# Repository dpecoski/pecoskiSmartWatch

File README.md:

# pecoskiSmartWatch
Dimitri Pecoski's Smart Watch Project

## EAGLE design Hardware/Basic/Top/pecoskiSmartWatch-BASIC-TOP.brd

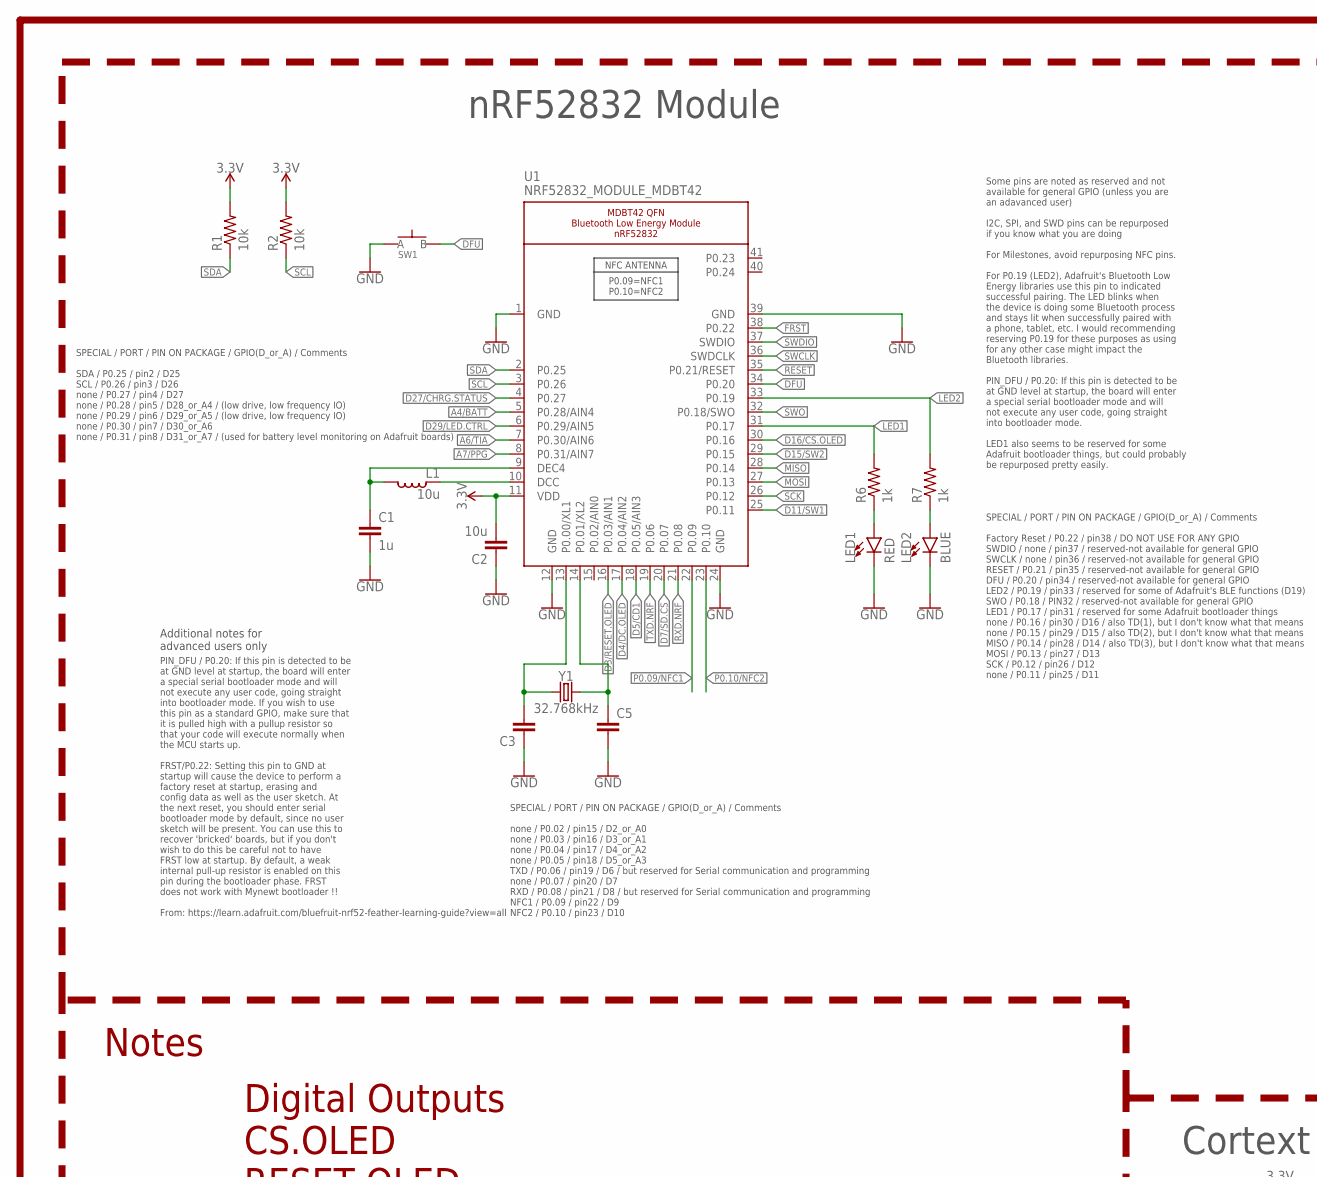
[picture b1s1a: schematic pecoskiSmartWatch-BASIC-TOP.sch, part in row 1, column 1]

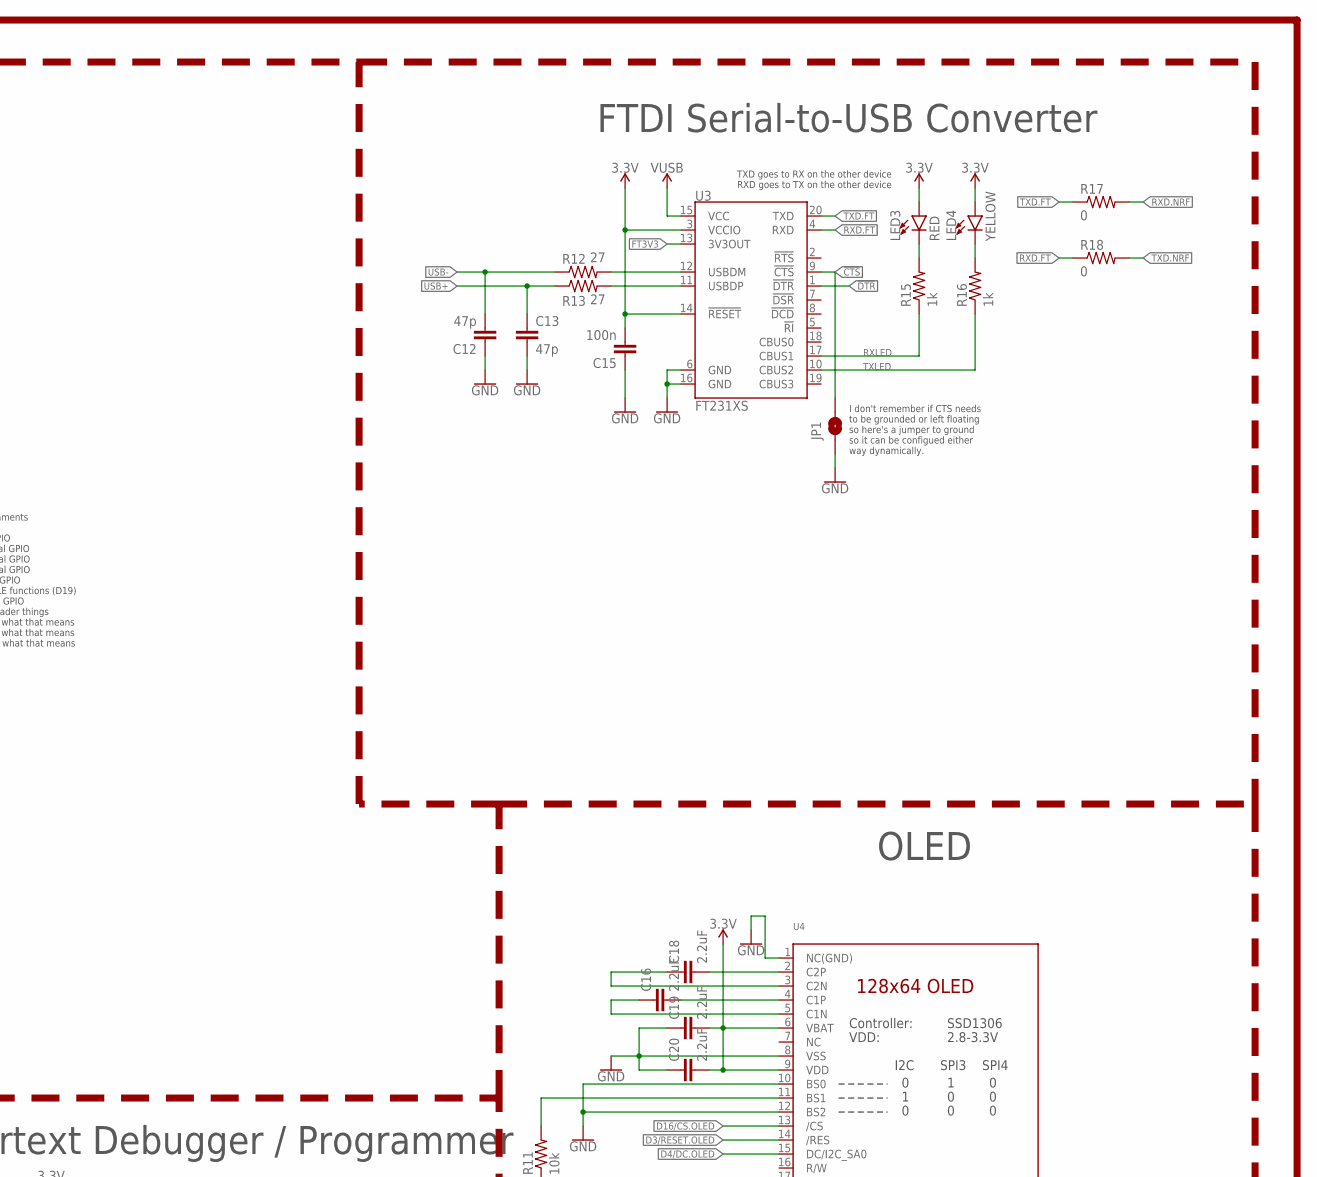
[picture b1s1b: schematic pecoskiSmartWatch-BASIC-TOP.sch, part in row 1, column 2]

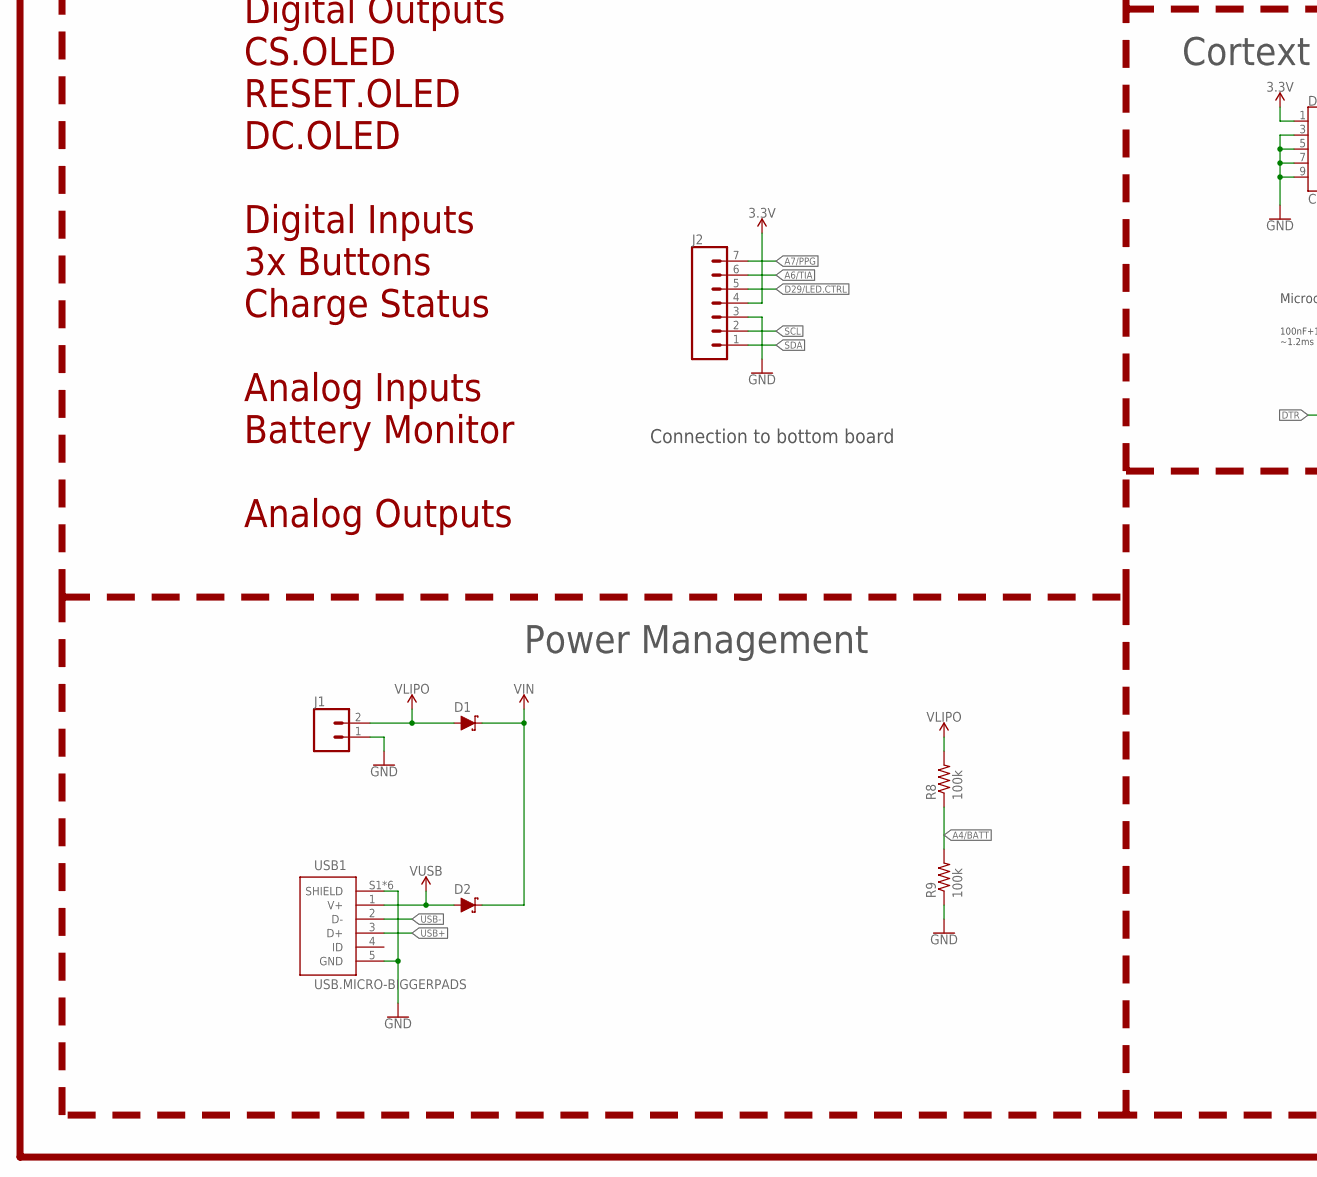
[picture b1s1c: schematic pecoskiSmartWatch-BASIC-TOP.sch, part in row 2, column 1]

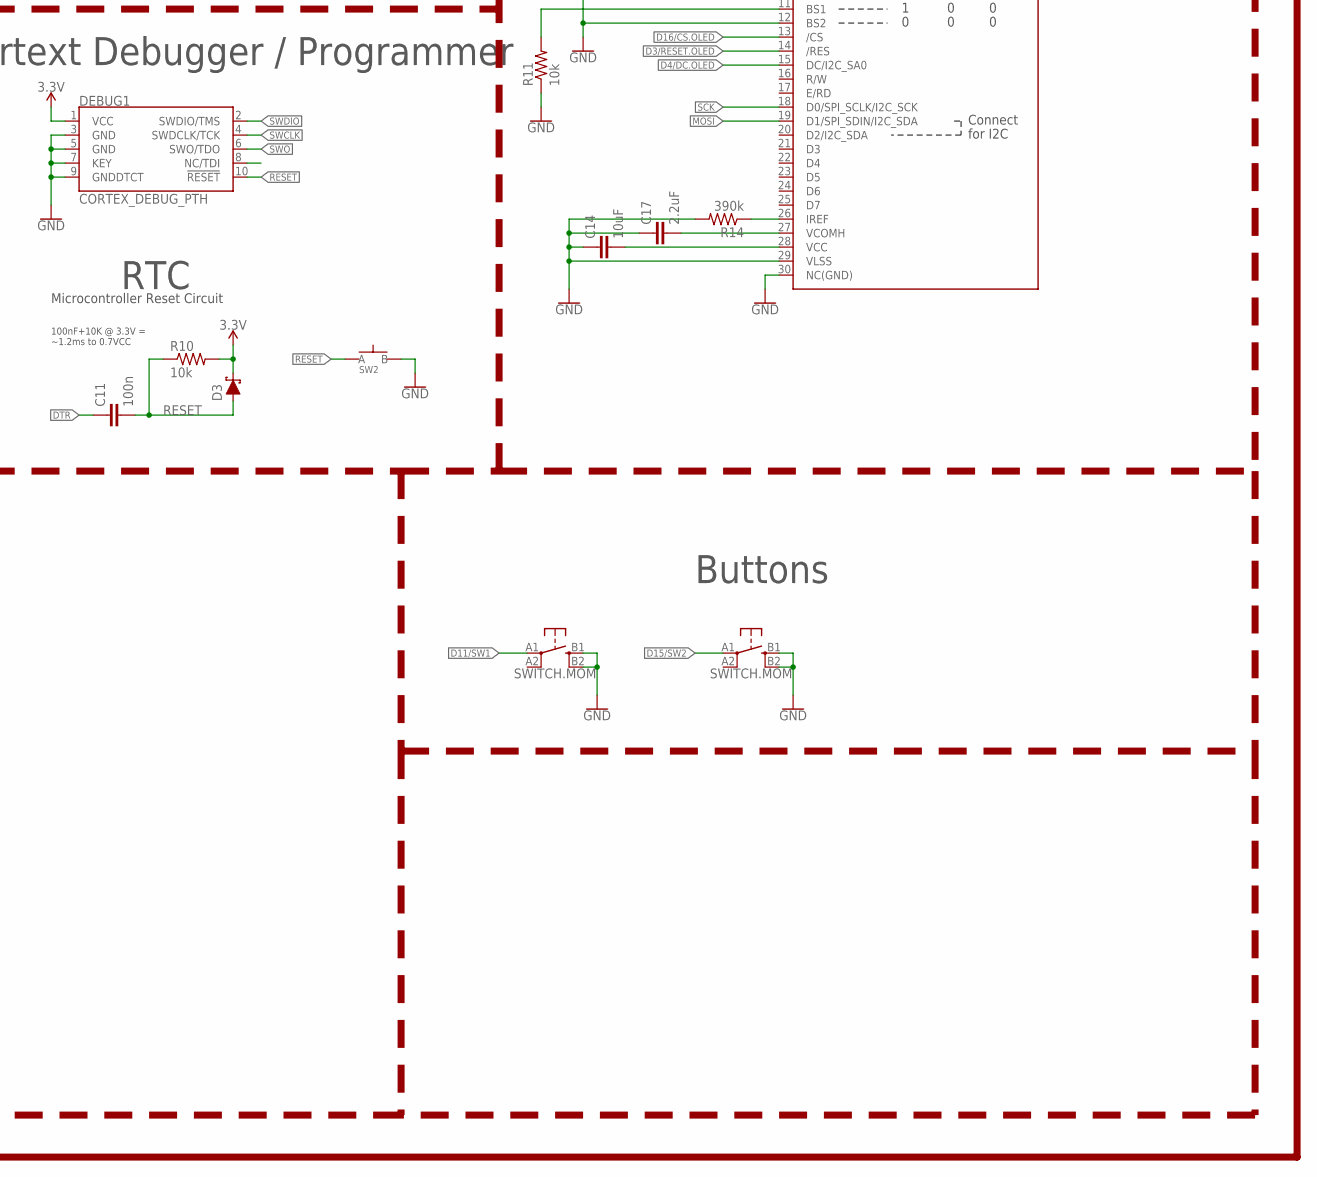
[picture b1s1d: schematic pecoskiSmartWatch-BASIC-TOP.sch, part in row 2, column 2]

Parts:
C1: 1u; C0603
C2: 10u; C0805
C3, C5: CAPACITOR0603; C0603
C11, C15: 100n; C0603
C12, C13: 47p; C0603
C14: 10uF; C0603
C16, C17, C18, C19, C20: 2.2uF; C0402
D1, D2, D3: SCHOTTKY-USC; USC
DEBUG1: CORTEX_DEBUG_PTH; 2X5-PTH-1.27MM
J1: CONN_02; 1X02
J2: CONN_07-1.27MM; 1X07_1.27MM
JP1: JUMPER-SMT_2_NO_SILK; SMT-JUMPER_2_NO_SILK
L1: 10u; L0603
LED1, LED3: RED; LED-0603
LED2: BLUE; LED-0603
LED4: YELLOW; LED-0603
R1, R2, R10, R11: 10k; R0603
R6, R7, R15, R16: 1k; R0603
R8, R9: 100k; R0603
R12, R13: 27; R0603
R14: 390k; R0603
R17, R18: 0; R0603
SW1, SW2: SPST-PTS830GG140-COPY.1-3; BUTTON-GULLWING
SW3, SW4: SWITCH.MOM; TACTILE_SWITCH_SMD_6.2MM_TALL
U1: NRF52832_MODULE_MDBT42; BLE_MODULE_RAYTAC_MDBT42
U3: FT231XS; SSOP20_L
U4: DISP_OLED_UG-2864HSWEG01-NO-WRAPAROUND; UG-2864HSWEG01_0.96IN_NO-WRAPAROUND
USB1: USB.MICRO-BIGGERPADS; USB-MICRO-01.BIGGERPADS
Y1: 32.768kHz; 2-SMD.NOLEAD.2.0MMTO1.2MM

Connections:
3.3V: C2.2, C15.2, C19.2, C20.2, D3.- (C), DEBUG1.1 (VCC), J2.4, LED3.A, LED4.A, R1.2, R2.2, R10.2, U1.11 (VDD), U3.3 (VCCIO), U3.14 (!RESET), U4.6 (VBAT), U4.9 (VDD)
!CTS: JP1.2, U3.9 (!CTS)
!DTR: U3.1 (!DTR)
A4/BATT: R8.1, R9.2, U1.5 (P0.28/AIN4)
A6/TIA: J2.6, U1.7 (P0.30/AIN6)
A7/PPG: J2.7, U1.8 (P0.31/AIN7)
D3/RESET.OLED: U1.16 (P0.03/AIN1), U4.14 (/RES)
D4/DC.OLED: U1.17 (P0.04/AIN2), U4.15 (DC/I2C_SA0)
D5/CD1: U1.18 (P0.05/AIN3)
D7/SD.CS: U1.20 (P0.07)
D11/SW1: SW3.A1 (1), U1.25 (P0.11)
D15/SW2: SW4.A1 (1), U1.29 (P0.15)
D16/CS.OLED: U1.30 (P0.16), U4.13 (/CS)
D27/CHRG.STATUS: U1.4 (P0.27)
D29/LED.CTRL: J2.5, U1.6 (P0.29/AIN5)
DFU: SW1.3 (B), U1.34 (P0.20)
DTR: C11.1
FRST: U1.38 (P0.22)
FT3V3: U3.13 (3V3OUT)
GND: C1.2, C2.1, C3.1, C5.2, C12.1, C13.2, C14.1, C15.1, C17.1, C19.1, C20.1, DEBUG1.3 (GND), DEBUG1.5 (GND), DEBUG1.7 (KEY), DEBUG1.9 (GNDDTCT), J1.1, J2.3, JP1.1, LED1.C, LED2.C, R9.1, R11.1, R14.2, SW1.1 (A), SW2.3 (B), SW3.B1 (3), SW3.B2 (4), SW4.B1 (3), SW4.B2 (4), U1.1 (GND), U1.12 (GND), U1.24 (GND), U1.39 (GND), U3.6 (GND), U3.16 (GND), U4.1 (NC(GND)), U4.8 (VSS), U4.10 (BS0), U4.12 (BS2), U4.29 (VLSS), U4.30 (NC(GND)), USB1.5 (GND), USB1.S1 (SHIELD), USB1.S2 (SHIELD), USB1.S3 (SHIELD), USB1.S4 (SHIELD), USB1.S5 (SHIELD), USB1.S6 (SHIELD)
LED1: R6.2, U1.31 (P0.17)
LED2: R7.2, U1.33 (P0.19)
MISO: U1.28 (P0.14)
MOSI: U1.27 (P0.13), U4.19 (D1/SPI_SDIN/I2C_SDA)
unnamed: R11.2, U4.11 (BS1)
unnamed: R14.1, U4.26 (IREF)
unnamed: C18.2, U4.2 (C2P)
unnamed: C3.2, U1.13 (P0.00/XL1), Y1.P$1 (1)
unnamed: C18.1, U4.3 (C2N)
unnamed: C5.1, U1.14 (P0.01/XL2), Y1.P$2 (2)
unnamed: C16.2, U4.4 (C1P)
unnamed: C16.1, U4.5 (C1N)
unnamed: LED1.A, R6.1
unnamed: LED2.A, R7.1
unnamed: L1.1, U1.10 (DCC)
unnamed: C1.1, L1.2, U1.9 (DEC4)
unnamed: C14.2, U4.28 (VCC)
unnamed: C17.2, U4.27 (VCOMH)
unnamed: R12.2, U3.12 (USBDM)
unnamed: R13.2, U3.11 (USBDP)
unnamed: LED3.C, R15.2
unnamed: LED4.C, R16.2
P0.09/NFC1: U1.22 (P0.09)
P0.10/NFC2: U1.23 (P0.10)
RESET: C11.2, D3.+ (A), DEBUG1.10 (!RESET), R10.1, SW2.1 (A), U1.35 (P0.21/RESET)
RXD.FT: R18.1, U3.4 (RXD)
RXD.NRF: R17.2, U1.21 (P0.08)
RXLED: R15.1, U3.17 (CBUS1)
SCK: U1.26 (P0.12), U4.18 (D0/SPI_SCLK/I2C_SCK)
SCL: J2.2, R2.1, U1.3 (P0.26)
SDA: J2.1, R1.1, U1.2 (P0.25)
SWCLK: DEBUG1.4 (SWDCLK/TCK), U1.36 (SWDCLK)
SWDIO: DEBUG1.2 (SWDIO/TMS), U1.37 (SWDIO)
SWO: DEBUG1.6 (SWO/TDO), U1.32 (P0.18/SWO)
TXD.FT: R17.1, U3.20 (TXD)
TXD.NRF: R18.2, U1.19 (P0.06)
TXLED: R16.1, U3.10 (CBUS2)
USB+: C13.1, R13.1, USB1.3 (D+)
USB-: C12.2, R12.1, USB1.2 (D-)
VIN: D1.- (C), D2.- (C)
VLIPO: D1.+ (A), J1.2, R8.2
V_USB: D2.+ (A), U3.15 (VCC), USB1.1 (V+)

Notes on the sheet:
Microcontroller Reset Circuit
100nF+10K @ 3.3V = ~1.2ms to 0.7VCC
SPECIAL / PORT / PIN ON PACKAGE / GPIO(D_or_A) / Comments SDA / P0.25 / pin2 / D25 SCL / P0.26 / pin3 / D26 none / P0.27 / pin4 / D27 none / P0.28 / pin5 / D28_or_A4 / (low drive, low frequency IO) none / P0.29 / pin6 / D29_or_A5 / (low drive, low frequency IO) none / P0.30 / pin7 / D30_or_A6 none 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
SPECIAL / PORT / PIN ON PACKAGE / GPIO(D_or_A) / Comments none / P0.02 / pin15 / D2_or_A0 none / P0.03 / pin16 / D3_or_A1 none / P0.04 / pin17 / D4_or_A2 none / P0.05 / pin18 / D5_or_A3 TXD / P0.06 / pin19 / D6 / but reserved for Serial communication and programming none / P0.07 / pin20 / D7 RXD / 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
SPECIAL / PORT / PIN ON PACKAGE / GPIO(D_or_A) / Comments Factory Reset / P0.22 / pin38 / DO NOT USE FOR ANY GPIO SWDIO / none / pin37 / reserved-not available for general GPIO SWCLK / none / pin36 / reserved-not available for general GPIO RESET / P0.21 / pin35 / reserved-not available for general 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
Some pins are noted as reserved and not available for general GPIO (unless you are an adavanced user) I2C, SPI, and SWD pins can be repurposed if you know what you are doing For Milestones, avoid repurposing NFC pins. For P0.19 (LED2), Adafruit's Bluetooth Low Energy libraries use this pin to indic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
PIN_DFU / P0.20: If this pin is detected to be at GND level at startup, the board will enter a special serial bootloader mode and will not execute any user code, going straight into bootloader mode. If you wish to use this pin as a standard GPIO, make sure that it is pulled high with a pullup resis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
Additional notes for advanced users only
nRF52832 Module
OLED
Power Management
Buttons
Cortext Debugger / Programmer
RTC
Digital Outputs CS.OLED RESET.OLED DC.OLED Digital Inputs 3x Buttons Charge Status Analog Inputs Battery Monitor Analog Outputs
TXD goes to RX on the other device RXD goes to TX on the other device
I don't remember if CTS needs to be grounded or left floating so here's a jumper to ground so it can be configued either way dynamically.
FTDI Serial-to-USB Converter
Notes
Connection to bottom board

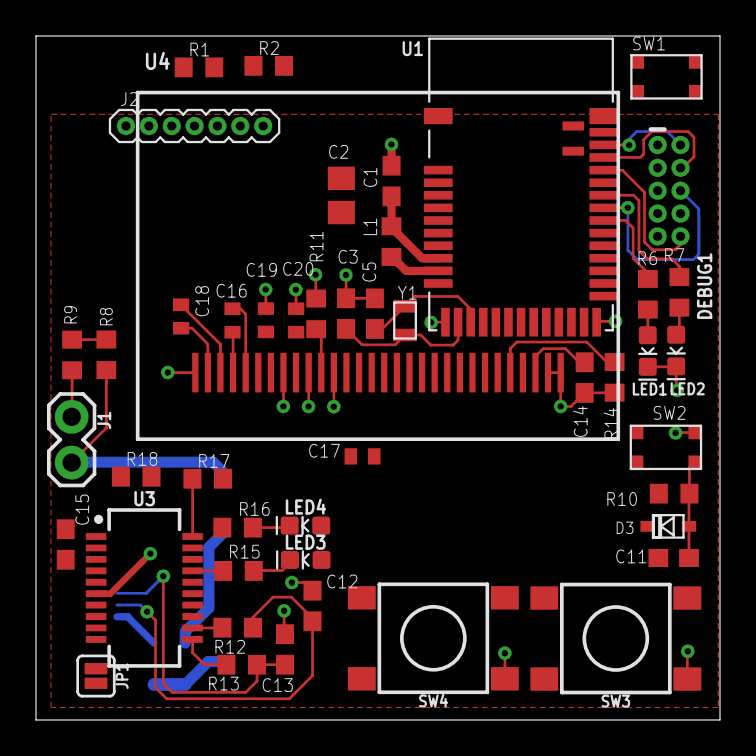
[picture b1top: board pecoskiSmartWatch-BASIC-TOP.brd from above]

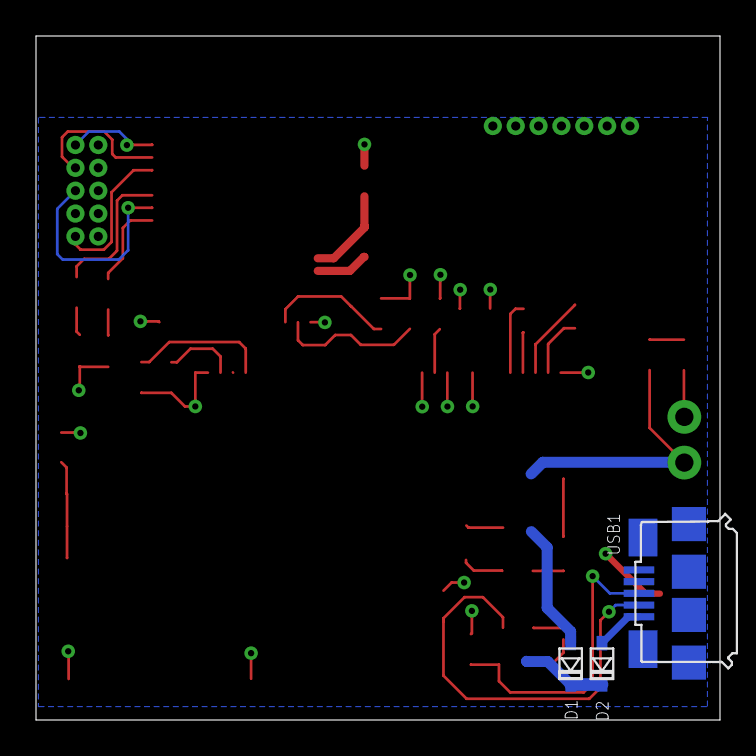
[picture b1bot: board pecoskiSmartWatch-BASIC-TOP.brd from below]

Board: 2 copper layers, 38.0 x 38.0 mm, 50 parts (3 on the bottom side), 52 nets.

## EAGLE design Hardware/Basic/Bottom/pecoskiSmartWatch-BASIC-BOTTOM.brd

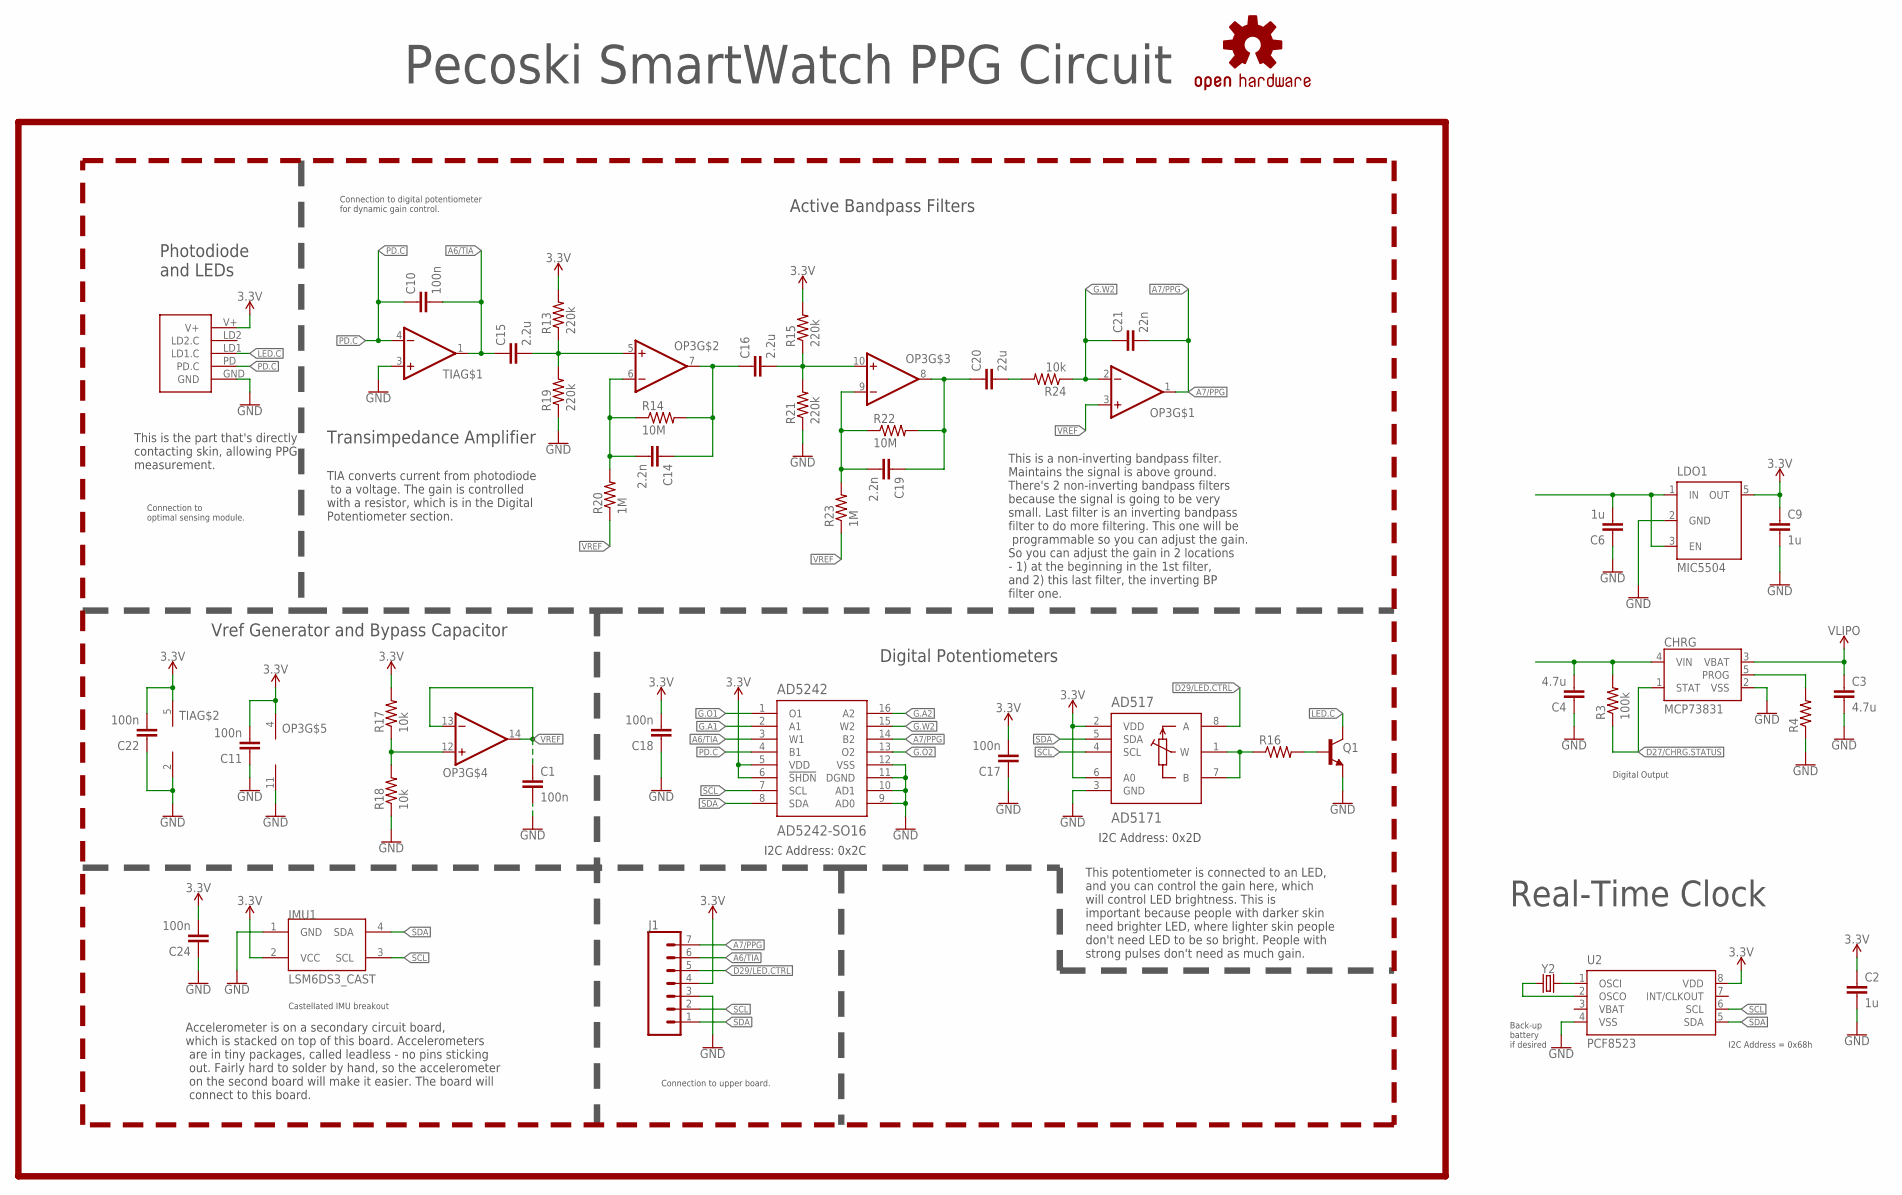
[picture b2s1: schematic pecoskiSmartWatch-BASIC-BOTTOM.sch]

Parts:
AD517: AD5171; SOT-23-8
AD5242: AD5242-SO16; SO16
C1, C10, C11, C17, C18, C22, C24: 100n; C0603
C2, C6, C9: 1u; C0603
C3, C4: 4.7u; C0603
C14, C19: 2.2n; C0603
C15, C16: 2.2u; C0603
C20: 22u; C0603
C21: 22n; C0603
CHRG: MCP73831; SOT23-5
IMU1: LSM6DS3_CAST
J1: CONN_07-1.27MM; 1X07_1.27MM
LDO1: MIC5504; SOT23-5
LOGO1: REVISION.A; REV.A
LOGO2: OSHW-LOGOS; OSHW-LOGO-S
OP3: OP-QUAD-SO14; SO14
Q1: NPN-GENERIC; SOT23-3
R3: 100k; R0603
R4, R16: RESISTOR0603; R0603
R13, R15, R19, R21: 220k; R0603
R14, R22: 10M; R0603
R17, R18: 10k; R0402
R20, R23: 1M; R0603
R24: 10k; R0603
TIA: OP-SINGLEOT; SOT23-5
U2: PCF8523; SO8; DIGIKEY 568-5306-1-ND
U$3: PPG.MODULE.2
Y2: 32.7680kHz; 2-SMD.NOLEAD.2.0MMTO1.2MM

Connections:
3.3V: AD517.2 (VDD), AD517.6 (A0), AD5242.5 (VDD), AD5242.6 (!SHDN), C2.1, C9.1, C11.2, C17.2, C18.2, C22.2, C24.2, IMU1.2 (VCC), J1.4, LDO1.5 (OUT), OP3.4 (V+), R13.2, R15.2, R17.2, TIA.5 (V+), U2.8 (VDD), U$3.V+
A6/TIA: AD5242.3 (W1), C10.2, C15.1, J1.6, TIA.1 (OUT)
A7/PPG: AD5242.14 (B2), C21.2, J1.7, OP3.1 (OUT)
D27/CHRG.STATUS: CHRG.1 (STAT), R3.1
D29/LED.CTRL: AD517.8 (A), J1.5
G.A1: AD5242.2 (A1)
G.A2: AD5242.16 (A2)
G.O1: AD5242.1 (O1)
G.O2: AD5242.13 (O2)
G.W2: AD5242.15 (W2), C21.1, OP3.2 (-IN), R24.1
GND: AD517.3 (GND), AD5242.9 (AD0), AD5242.10 (AD1), AD5242.11 (DGND), AD5242.12 (VSS), C1.2, C2.2, C3.2, C4.1, C6.1, C9.2, C11.1, C17.1, C18.1, C22.1, C24.1, CHRG.2 (VSS), IMU1.1 (GND), J1.3, LDO1.2 (GND), OP3.11 (V-), Q1.2 (E), R4.1, R18.1, R19.1, R21.1, TIA.2 (V-), TIA.3 (+IN), U2.4 (VSS), U$3.GND
LED.C: Q1.3 (C), U$3.LD1 (LD1.C)
unnamed: U2.2 (OSCO), Y2.P$1 (1)
unnamed: U2.1 (OSCI), Y2.P$2 (2)
unnamed: CHRG.5 (PROG), R4.2
unnamed: Q1.1 (B), R16.2
unnamed: AD517.1 (W), AD517.7 (B), R16.1
unnamed: OP3.12 (+IN), R17.1, R18.2
unnamed: C15.2, OP3.5 (+IN), R13.1, R19.2
unnamed: C14.2, OP3.6 (-IN), R14.1, R20.2
unnamed: C14.1, C16.1, OP3.7 (OUT), R14.2
unnamed: C16.2, OP3.10 (+IN), R15.1, R21.2
unnamed: C19.2, OP3.9 (-IN), R22.1, R23.2
unnamed: C19.1, C20.1, OP3.8 (OUT), R22.2
unnamed: C20.2, R24.2
PD.C: AD5242.4 (B1), C10.1, TIA.4 (-IN), U$3.PD (PD.C)
SCL: AD517.4 (SCL), AD5242.7 (SCL), IMU1.3 (SCL), J1.2, U2.6 (SCL)
SDA: AD517.5 (SDA), AD5242.8 (SDA), IMU1.4 (SDA), J1.1, U2.5 (SDA)
VBAT: U2.3 (VBAT)
VIN1: C4.2, C6.2, CHRG.4 (VIN), LDO1.1 (IN), LDO1.3 (EN), R3.2
VLIPO: C3.1, CHRG.3 (VBAT)
VREF: C1.1, OP3.3 (+IN), OP3.13 (-IN), OP3.14 (OUT), R20.1, R23.1

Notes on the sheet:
Photodiode and LEDs
Active Bandpass Filters
Digital Potentiometers
Transimpedance Amplifier
I2C Address: 0x2C
I2C Address: 0x2D
This is the part that's directly contacting skin, allowing PPG measurement.
TIA converts current from photodiode to a voltage. The gain is controlled with a resistor, which is in the Digital Potentiometer section.
This is a non-inverting bandpass filter. Maintains the signal is above ground. There's 2 non-inverting bandpass filters because the signal is going to be very small. Last filter is an inverting bandpass filter to do more filtering. This one will be programmable so you can adjust the gain. So you ca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
This potentiometer is connected to an LED, and you can control the gain here, which will control LED brightness. This is important because people with darker skin need brighter LED, where lighter skin people don't need LED to be so bright. People with strong pulses don't need as much gain.
Accelerometer is on a secondary circuit board, which is stacked on top of this board. Accelerometers are in tiny packages, called leadless - no pins sticking out. Fairly hard to solder by hand, so the accelerometer on the second board will make it easier. The board will connect to this board.
Connection to optimal sensing module.
Connection to digital potentiometer for dynamic gain control.
Connection to upper board.
Castellated IMU breakout
Vref Generator and Bypass Capacitor
Pecoski SmartWatch PPG Circuit
I2C Address = 0x68h
Back-up battery if desired
Real-Time Clock
Digital Output

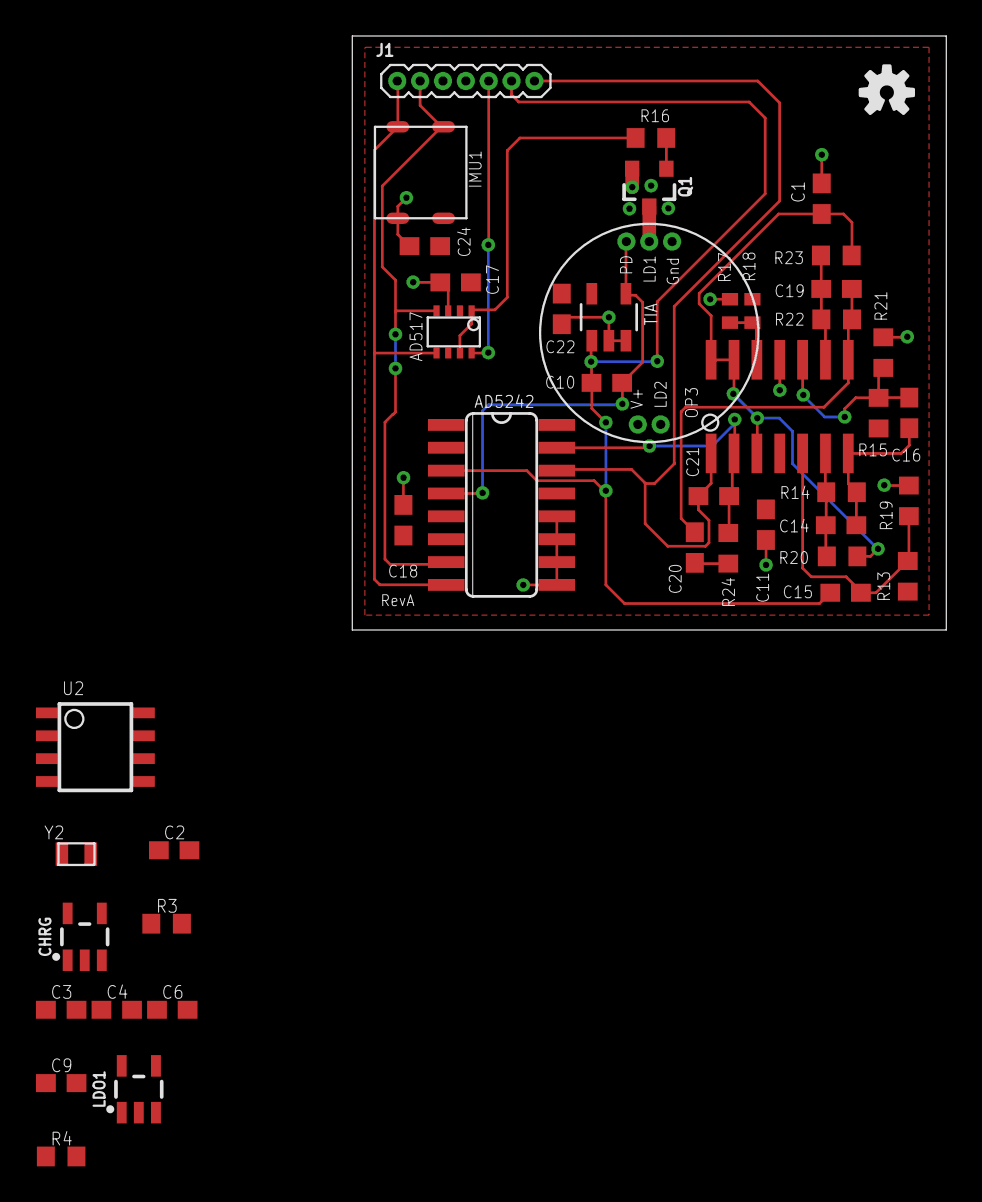
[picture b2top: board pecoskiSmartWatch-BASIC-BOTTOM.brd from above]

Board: 2 copper layers, 33.0 x 33.0 mm, 46 parts (0 on the bottom side), 27 nets.

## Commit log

2021-02-06 features list
2021-02-07 add Arduion file
2021-02-07 Add AUX2 files
2021-02-07 Add AUX 1 files
2021-02-07 Add Bottom Files
2021-02-07 Add PPG Module Files
2021-02-07 Add Top Files
2021-02-13 Updated top board hardware Eagle
2021-02-14 Update schematic trackign and board hardware
2021-02-27 Updated Eagle Hardware 2021_02_27
2021-02-28 Hardware Updates 2021_02_27
2021-03-06 HW Updates 2021/03/06
2021-03-07 HW Updates 2021/03/06 Pt 2
2021-03-13 Updated HW 2021_03_13 AM
2021-03-14 Updated HW 2021_03_13 PM
